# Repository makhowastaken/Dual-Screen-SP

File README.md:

# Dual-Screen-SP
An adapter for installing a second screen in a Game Boy Advance SP

untested, will expand this later

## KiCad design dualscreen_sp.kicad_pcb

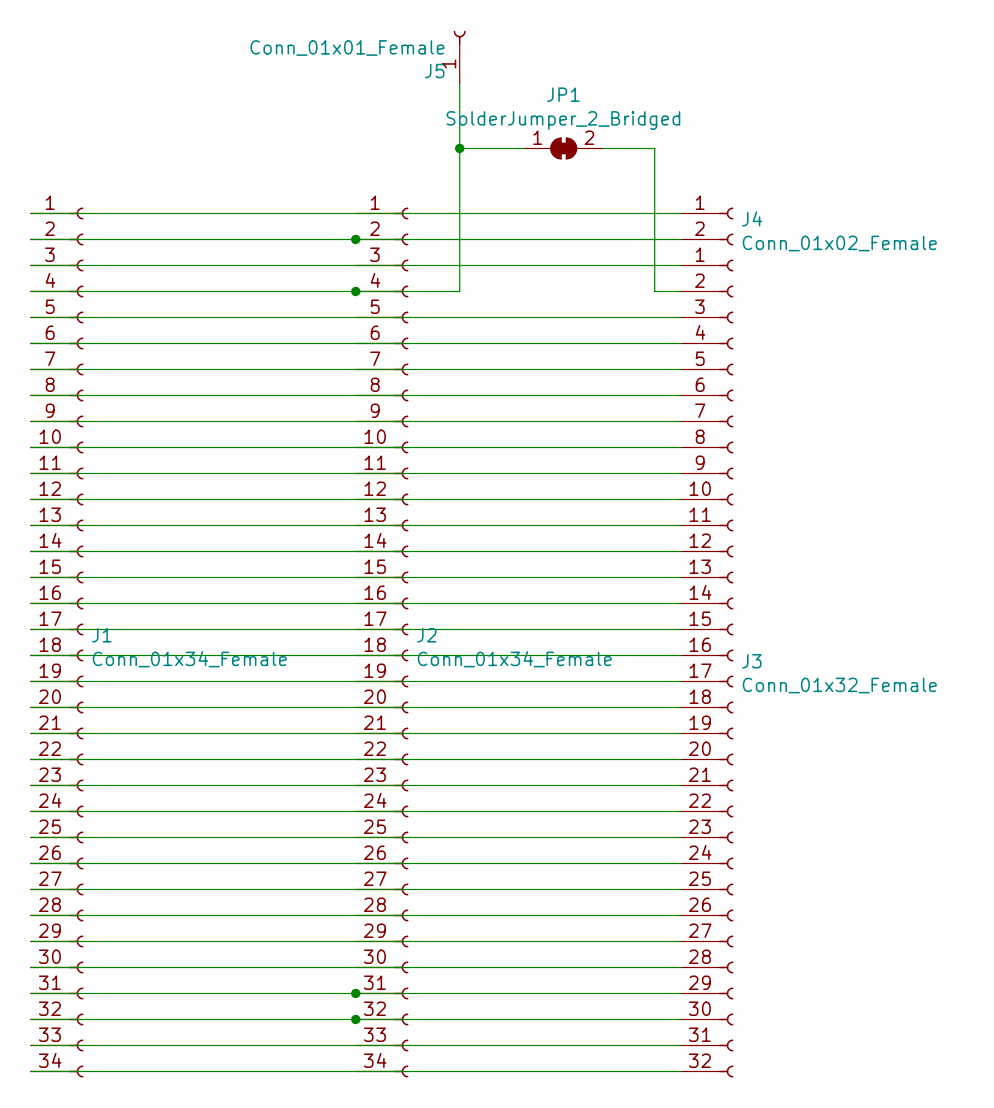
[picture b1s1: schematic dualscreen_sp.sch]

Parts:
J1, J2: Conn_01x34_Female; TE_3-1734839-4_1x34-1MP_P0.5mm_Horizontal
J3: Conn_01x32_Female; TE_3-1734839-2_1x32-1MP_P0.5mm_Horizontal
J4: Conn_01x02_Female; PinHeader_1x02_P2.54mm_Vertical
J5: Conn_01x01_Female; PinSocket_1x01_P2.54mm_Vertical
JP1: SolderJumper_2_Bridged; SolderJumper-2_P1.3mm_Open_TrianglePad1.0x1.5mm

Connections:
unnamed: J1.1, J2.1, J4.1
unnamed: J1.2, J2.2, J4.2
unnamed: J1.3, J2.3, J3.1
unnamed: J1.4, J1.MP, J2.4, J2.MP, J3.MP, J5.1, JP1.1 (A)
unnamed: J1.5, J2.5, J3.3
unnamed: J1.6, J2.6, J3.4
unnamed: J1.7, J2.7, J3.5
unnamed: J1.8, J2.8, J3.6
unnamed: J1.9, J2.9, J3.7
unnamed: J1.10, J2.10, J3.8
unnamed: J1.11, J2.11, J3.9
unnamed: J1.12, J2.12, J3.10
unnamed: J1.13, J2.13, J3.11
unnamed: J1.14, J2.14, J3.12
unnamed: J1.15, J2.15, J3.13
unnamed: J1.16, J2.16, J3.14
unnamed: J1.17, J2.17, J3.15
unnamed: J1.18, J2.18, J3.16
unnamed: J1.19, J2.19, J3.17
unnamed: J1.20, J2.20, J3.18
unnamed: J1.21, J2.21, J3.19
unnamed: J1.22, J2.22, J3.20
unnamed: J1.23, J2.23, J3.21
unnamed: J1.24, J2.24, J3.22
unnamed: J1.25, J2.25, J3.23
unnamed: J1.26, J2.26, J3.24
unnamed: J1.27, J2.27, J3.25
unnamed: J1.28, J2.28, J3.26
unnamed: J1.29, J2.29, J3.27
unnamed: J1.30, J2.30, J3.28
unnamed: J1.31, J2.31, J3.29
unnamed: J1.32, J2.32, J3.30
unnamed: J1.33, J2.33, J3.31
unnamed: J1.34, J2.34, J3.32
unnamed: J3.2, JP1.2 (B)

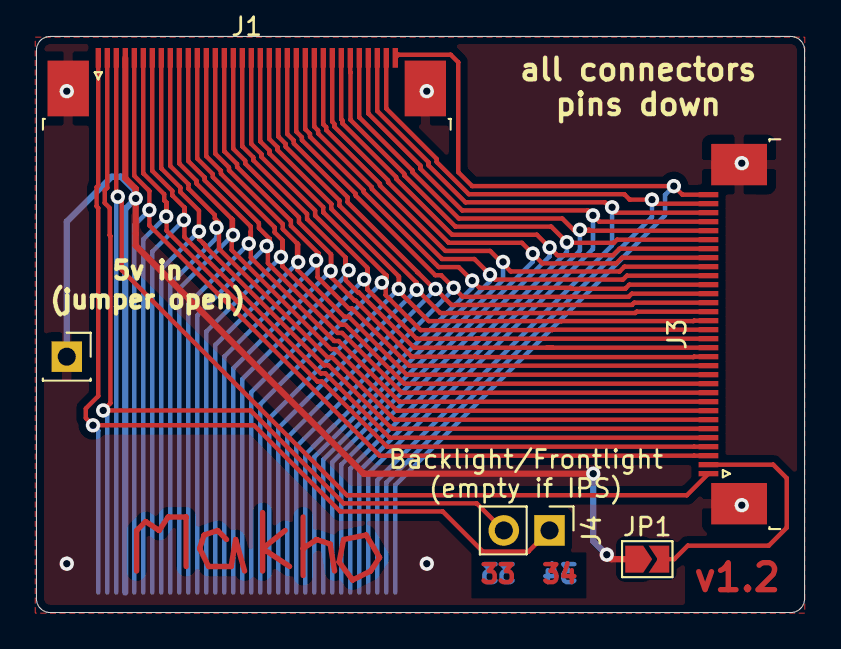
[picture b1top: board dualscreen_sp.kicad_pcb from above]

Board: 2 copper layers, 42.7 x 32.0 mm, 6 parts (1 on the bottom side), 35 nets.
